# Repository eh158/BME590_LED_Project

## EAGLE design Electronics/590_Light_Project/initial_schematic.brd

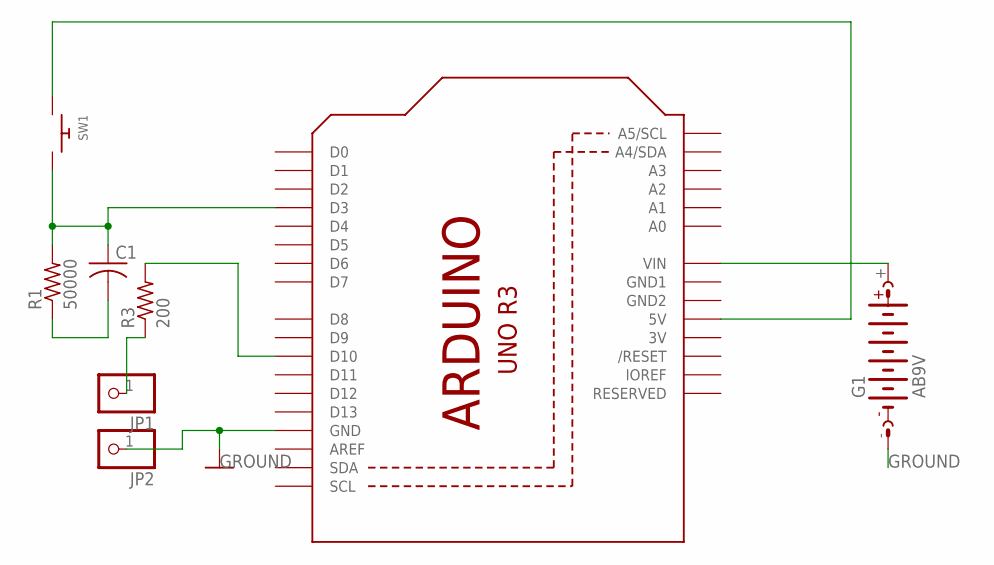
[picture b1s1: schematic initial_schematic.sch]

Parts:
C1: C-USC0805; C0805
G1: AB9V
JP1, JP2: PINHD-1X1; 1X01
R1: 50000; R0805W
R3: 200; R0805W
SW1: SWITCH_PUSHBUTTONC&K_KSS; BTN_CK_KSS
U1: ARDUINOR3-DIMENSION; ARDUINOR3

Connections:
3V: U1.3V
GND1: U1.GND1
GND2: U1.GND2
GROUND: JP2.1, U1.GND
unnamed: G1.+, U1.VIN
unnamed: SW1.P$1, U1.5V
unnamed: R3.2, U1.D10
unnamed: C1.1, R1.2, SW1.P$2, U1.D3
unnamed: C1.2, R1.1
unnamed: JP1.1, R3.1

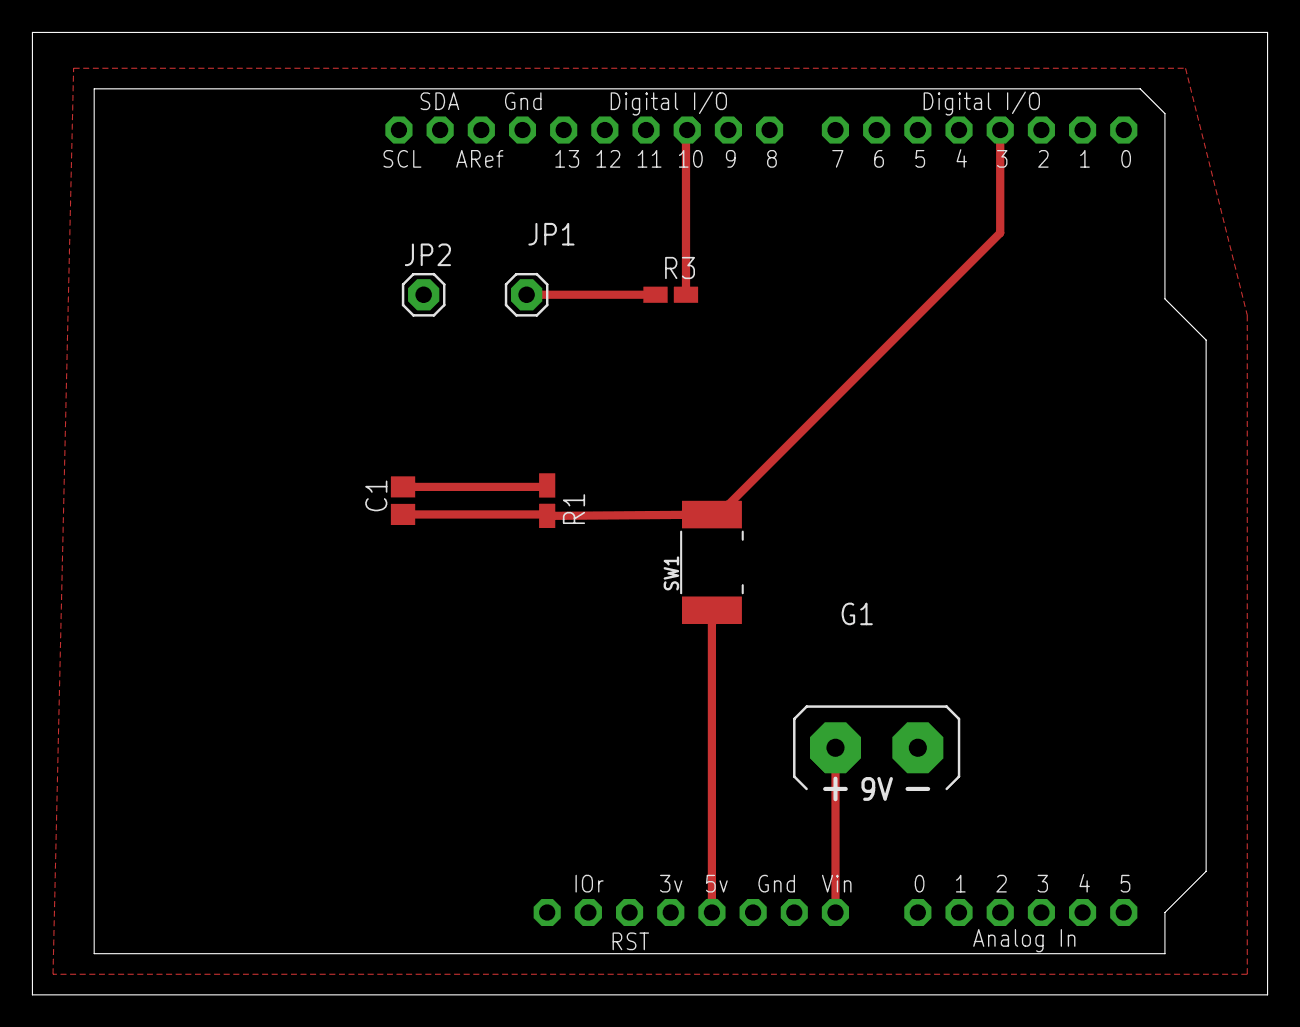
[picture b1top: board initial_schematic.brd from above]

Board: 2 copper layers, 76.2 x 59.4 mm, 8 parts (0 on the bottom side), 7 nets.

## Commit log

2018-10-02 First Commit, Milestones 1 and 2
2018-11-02 Milestone 3
2018-11-08 Initial Electronics Schematic
2018-11-08 Software
2018-11-21 Initial MEchanical Assembly
2018-11-30 Modified ECAD according to Matt Brown's comments
2018-11-30 Modified dimensions
2018-12-11 schematic IDF's
2018-12-11 Updated Mechanical CAD Assemblies
2018-12-14 Updated CAD files including STL's used for 3D printing
2018-12-14 Changed software from pseudocode to actual code
